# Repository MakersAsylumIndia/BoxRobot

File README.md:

# BoxRobot
convert an innovation school kit box in to a robot

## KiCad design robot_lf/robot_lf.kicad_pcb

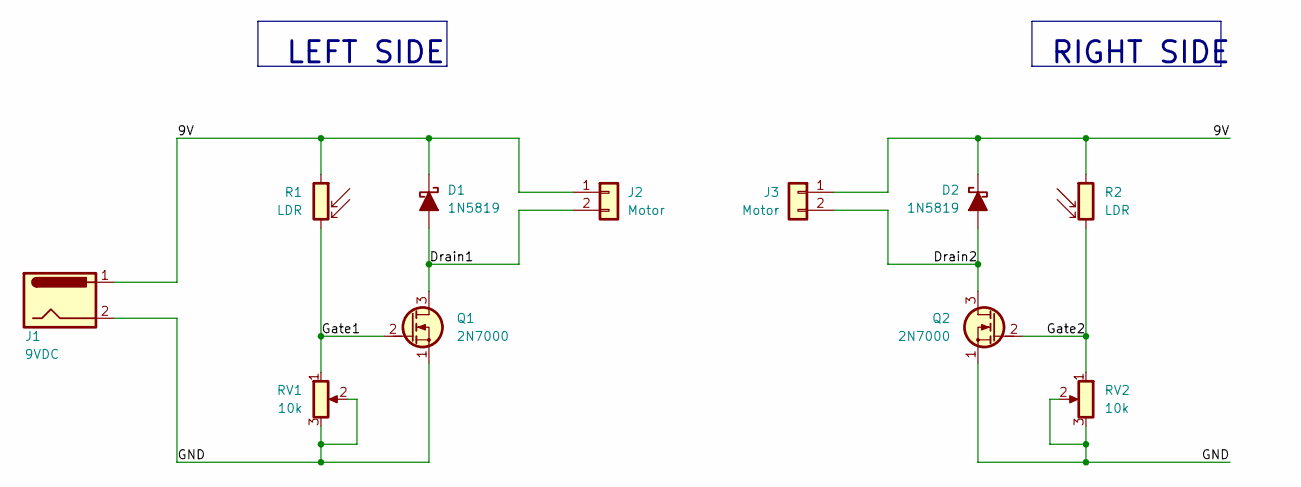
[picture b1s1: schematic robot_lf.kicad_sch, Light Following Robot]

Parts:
D1, D2: 1N5819; D_DO-41_SOD81_P10.16mm_Horizontal
J1: 9VDC; BarrelJack_Horizontal
J2, J3: Motor; PinHeader_1x02_P2.54mm_Vertical
Q1, Q2: 2N7000; TO-92
R1, R2: LDR; R_LDR_4.9x4.2mm_P2.54mm_Vertical
RV1, RV2: 10k; Pot_P160KNPD4FC20B10K

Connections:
/9V: D1.1 (K), D2.1 (K), J1.1, J2.1, J3.1, R1.1, R2.1
/Drain1: D1.2 (A), J2.2, Q1.3 (D)
/Drain2: D2.2 (A), J3.2, Q2.3 (D)
/GND: J1.2, Q1.1 (S), Q2.1 (S), RV1.2, RV1.3, RV2.2, RV2.3
/Gate1: Q1.2 (G), R1.2, RV1.1
/Gate2: Q2.2 (G), R2.2, RV2.1

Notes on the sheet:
LEFT SIDE
RIGHT SIDE

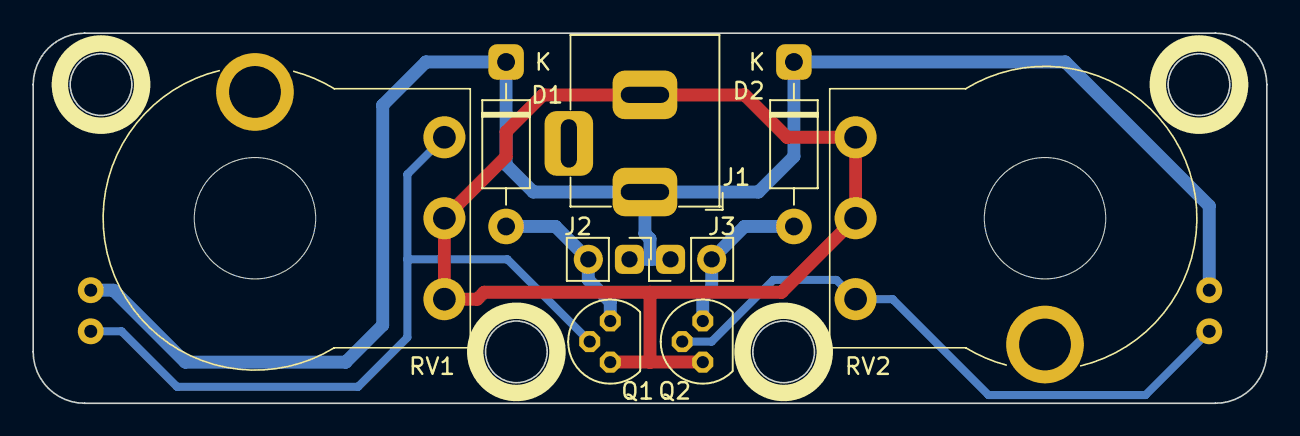
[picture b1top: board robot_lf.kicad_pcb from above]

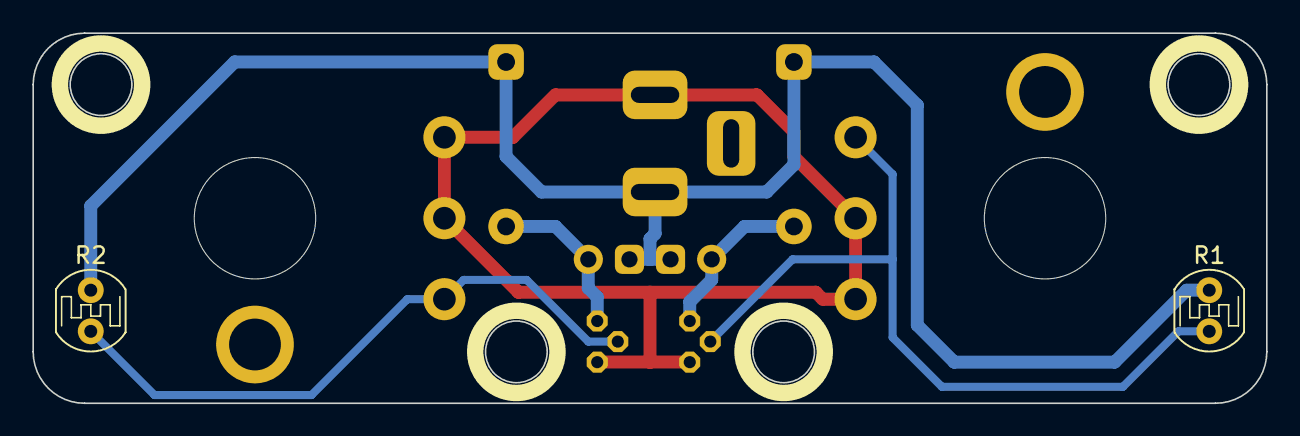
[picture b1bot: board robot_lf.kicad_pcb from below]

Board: 2 copper layers, 76.2 x 22.9 mm, 11 parts (4 on the bottom side), 6 nets.

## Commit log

2023-06-22 edited RFC document
